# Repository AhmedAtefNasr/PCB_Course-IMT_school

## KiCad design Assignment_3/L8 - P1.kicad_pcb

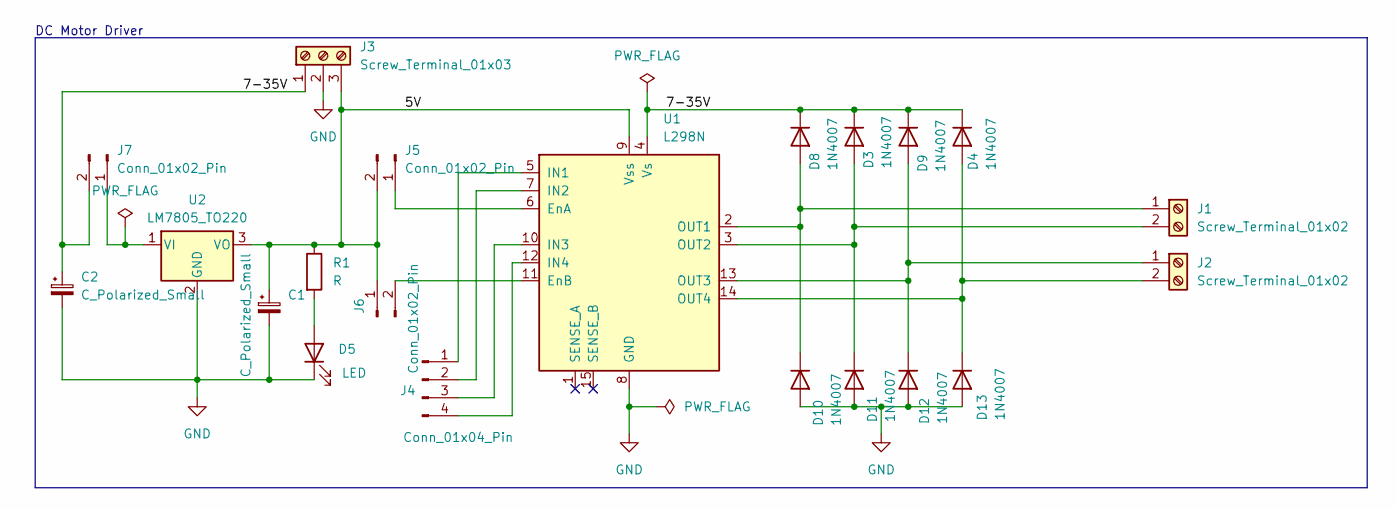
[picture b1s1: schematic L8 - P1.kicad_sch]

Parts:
C1, C2: C_Polarized_Small; CP_Radial_D4.0mm_P1.50mm
D3, D4, D8, D9, D10, D11, D12, D13: 1N4007; D_DO-41_SOD81_P10.16mm_Horizontal
D5: LED; LED_D3.0mm
J1, J2: Screw_Terminal_01x02; TerminalBlock_Phoenix_MPT-0,5-2-2.54_1x02_P2.54mm_Horizontal
J3: Screw_Terminal_01x03; TerminalBlock_Phoenix_MPT-0,5-3-2.54_1x03_P2.54mm_Horizontal
J4: Conn_01x04_Pin; PinHeader_1x04_P1.00mm_Vertical
J5, J6, J7: Conn_01x02_Pin; PinHeader_1x02_P1.00mm_Vertical
R1: R; R_Axial_DIN0204_L3.6mm_D1.6mm_P5.08mm_Horizontal
U1: L298N; TO-220-15_P2.54x5.08mm_StaggerOdd_Lead4.58mm_Vertical
U2: LM7805_TO220; TO-220-3_Horizontal_TabDown

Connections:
/5V: C1.1, J3.3, J5.2, J6.1, R1.1, U1.9 (Vss), U2.3 (VO)
/7-35V: C2.1, D3.1 (K), D4.1 (K), D8.1 (K), D9.1 (K), J3.1, J7.2, U1.4 (Vs)
GND: C1.2, C2.2, D5.1 (K), D10.2 (A), D11.2 (A), D12.2 (A), D13.2 (A), J3.2, U1.8 (GND), U2.2 (GND)
unnamed: D5.2 (A), R1.2
unnamed: D8.2 (A), D10.1 (K), J1.1, U1.2 (OUT1)
unnamed: D3.2 (A), D11.1 (K), J1.2, U1.3 (OUT2)
unnamed: D9.2 (A), D12.1 (K), J2.1, U1.13 (OUT3)
unnamed: D4.2 (A), D13.1 (K), J2.2, U1.14 (OUT4)
unnamed: J4.1, U1.5 (IN1)
unnamed: J4.2, U1.7 (IN2)
unnamed: J4.3, U1.10 (IN3)
unnamed: J4.4, U1.12 (IN4)
unnamed: J5.1, U1.6 (EnA)
unnamed: J6.2, U1.11 (EnB)
unnamed: J7.1, U2.1 (VI)

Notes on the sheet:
DC Motor Driver

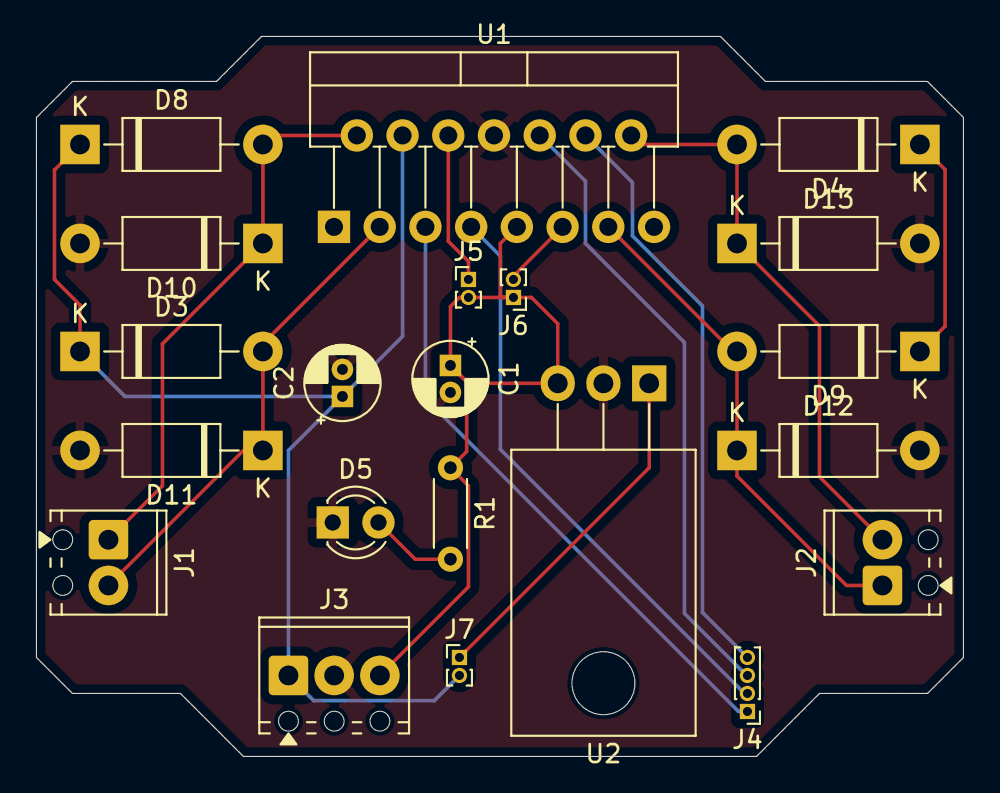
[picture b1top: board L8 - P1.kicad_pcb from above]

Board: 2 copper layers, 51.5 x 40.0 mm, 21 parts (0 on the bottom side), 15 nets.

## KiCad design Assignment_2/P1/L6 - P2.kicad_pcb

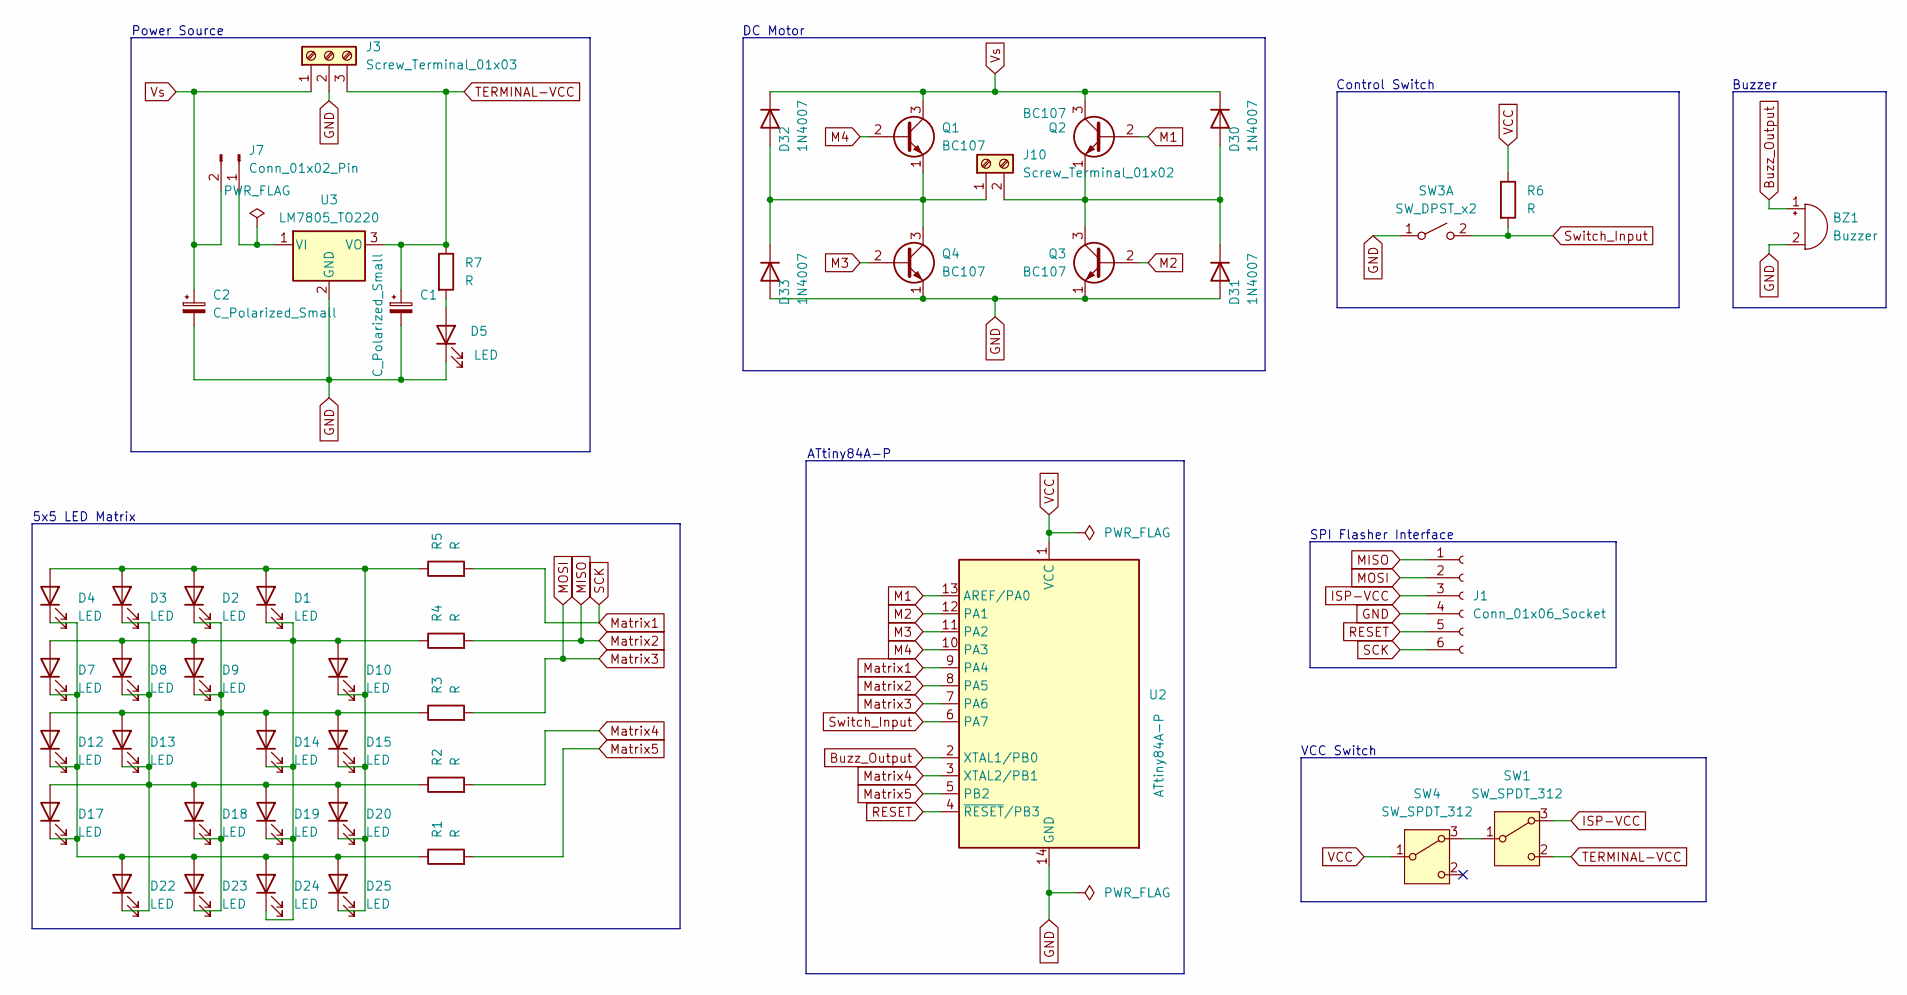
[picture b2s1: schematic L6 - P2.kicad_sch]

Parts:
BZ1: Buzzer; MagneticBuzzer_ProSignal_ABT-410-RC
C1, C2: C_Polarized_Small; CP_Radial_D4.0mm_P1.50mm
D1, D2, D3, D4, D7, D8, D9, D10, D12, D13, D14, D15, D17, D18, D19, D20, D22, D23, D24, D25: LED; LED_D5.0mm_Clear
D5: LED; LED_D3.0mm
D30, D31, D32, D33: 1N4007; D_DO-41_SOD81_P10.16mm_Horizontal
J1: Conn_01x06_Socket; PinHeader_1x06_P2.54mm_Horizontal
J3: Screw_Terminal_01x03; TerminalBlock_Phoenix_MPT-0,5-3-2.54_1x03_P2.54mm_Horizontal
J7: Conn_01x02_Pin; PinHeader_1x02_P1.00mm_Vertical
J10: Screw_Terminal_01x02; TerminalBlock_Phoenix_MPT-0,5-2-2.54_1x02_P2.54mm_Horizontal
Q1, Q2, Q3, Q4: BC107; TO-18-3
R1, R2, R3, R4, R5, R6, R7: R; R_Axial_DIN0204_L3.6mm_D1.6mm_P5.08mm_Horizontal
SW1, SW4: SW_SPDT_312; SW_Slide_SPDT_Straight_CK_OS102011MS2Q
SW3: SW_DPST_x2; SW_PUSH_6mm_H5mm
U2: ATtiny84A-P; DIP-14_W7.62mm
U3: LM7805_TO220; TO-220-3_Horizontal_TabDown

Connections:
Buzz_Output: BZ1.1 (+), U2.2 (XTAL1/PB0)
GND: BZ1.2 (-), C1.2, C2.2, D5.1 (K), D31.2 (A), D33.2 (A), J1.4, J3.2, Q3.1 (E), Q4.1 (E), SW3.1 (A), U2.14 (GND), U3.2 (GND)
ISP-VCC: J1.3, SW1.3 (A)
M1: Q2.2 (B), U2.13 (AREF/PA0)
M2: Q3.2 (B), U2.12 (PA1)
M3: Q4.2 (B), U2.11 (PA2)
M4: Q1.2 (B), U2.10 (PA3)
MISO: J1.1, R4.2, U2.8 (PA5)
MOSI: J1.2, R3.2, U2.7 (PA6)
Matrix1: J1.6, R5.2, U2.9 (PA4)
Matrix4: R2.2, U2.3 (XTAL2/PB1)
Matrix5: R1.2, U2.5 (PB2)
unnamed: D1.2 (A), D2.2 (A), D3.2 (A), D4.2 (A), D10.1 (K), D15.1 (K), D20.1 (K), D25.1 (K), R5.1
unnamed: D1.1 (K), D7.2 (A), D8.2 (A), D9.2 (A), D10.2 (A), D14.1 (K), D19.1 (K), D24.1 (K), R4.1
unnamed: D5.2 (A), R7.2
unnamed: D2.1 (K), D9.1 (K), D12.2 (A), D13.2 (A), D14.2 (A), D15.2 (A), D18.1 (K), D23.1 (K), R3.1
unnamed: D4.1 (K), D7.1 (K), D12.1 (K), D17.1 (K), D22.2 (A), D23.2 (A), D24.2 (A), D25.2 (A), R1.1
unnamed: D3.1 (K), D8.1 (K), D13.1 (K), D17.2 (A), D18.2 (A), D19.2 (A), D20.2 (A), D22.1 (K), R2.1
unnamed: D30.2 (A), D31.1 (K), J10.2, Q2.1 (E), Q3.3 (C)
unnamed: D32.2 (A), D33.1 (K), J10.1, Q1.1 (E), Q4.3 (C)
unnamed: J7.1, U3.1 (VI)
unnamed: SW1.1 (B), SW4.3 (A)
RESET: J1.5, U2.4 (~RESET/PB3)
Switch_Input: R6.2, SW3.2 (B), U2.6 (PA7)
TERMINAL-VCC: C1.1, J3.3, R7.1, SW1.2 (C), U3.3 (VO)
VCC: R6.1, SW4.1 (B), U2.1 (VCC)
Vs: C2.1, D30.1 (K), D32.1 (K), J3.1, J7.2, Q1.3 (C), Q2.3 (C)

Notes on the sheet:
Power Source
Control Switch
Buzzer
5x5 LED Matrix
DC Motor
SPI Flasher Interface
VCC Switch
ATtiny84A-P

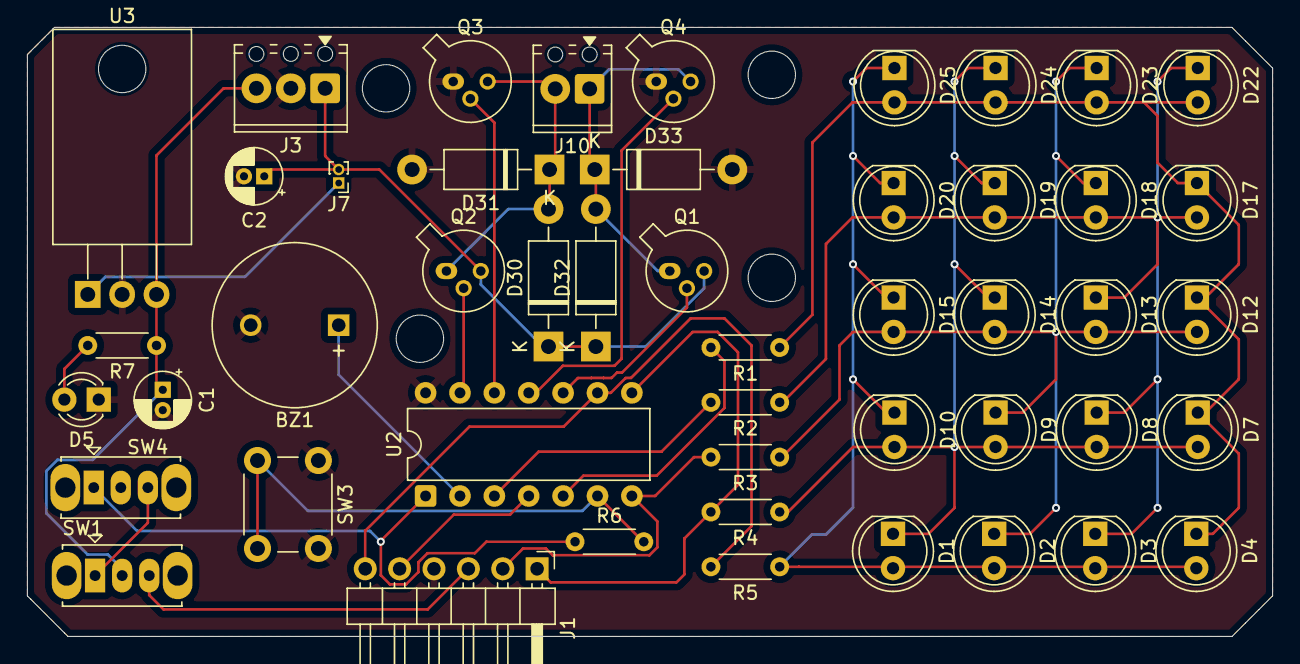
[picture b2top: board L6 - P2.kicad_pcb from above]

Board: 2 copper layers, 92.0 x 45.0 mm, 48 parts (0 on the bottom side), 27 nets.

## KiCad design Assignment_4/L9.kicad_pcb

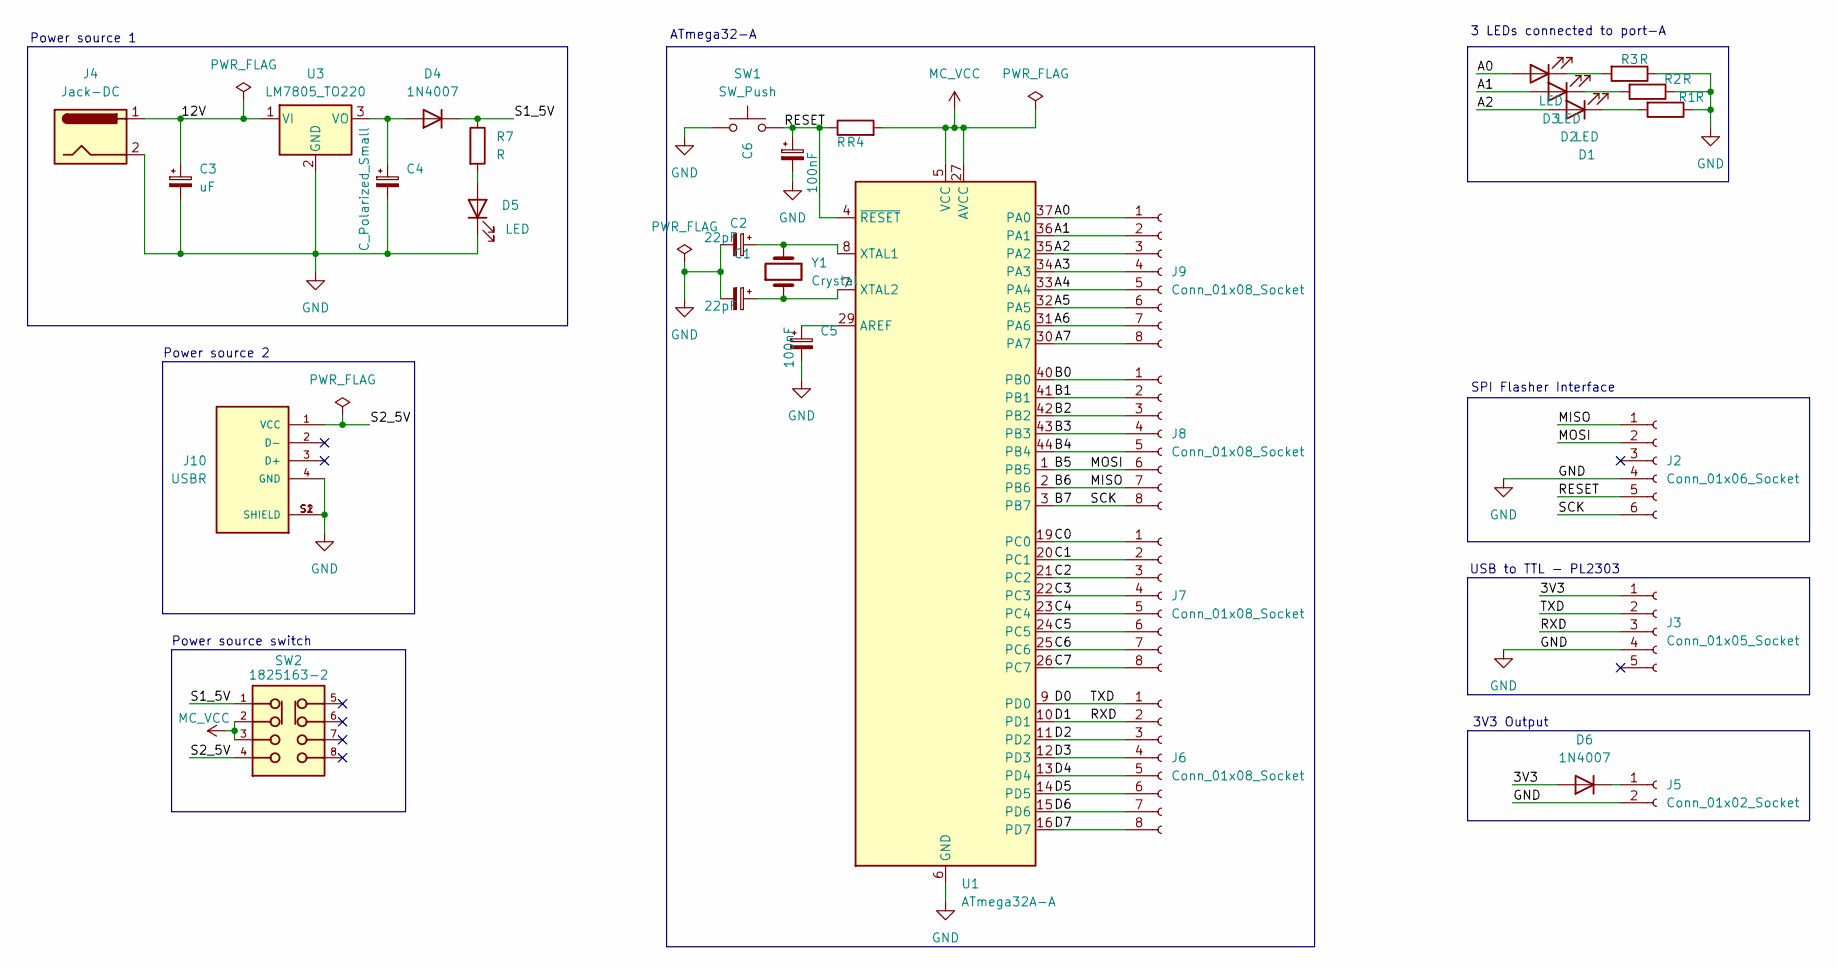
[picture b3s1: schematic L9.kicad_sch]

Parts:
C1, C2: 22pF; C_Disc_D5.1mm_W3.2mm_P5.00mm
C3: uF; CP_Radial_D4.0mm_P1.50mm
C4: C_Polarized_Small; CP_Radial_D4.0mm_P1.50mm
C5, C6: 100nF; C_Disc_D3.0mm_W2.0mm_P2.50mm
D1, D2, D3: LED; LED_D5.0mm
D4, D6: 1N4007; D_DO-41_SOD81_P10.16mm_Horizontal
D5: LED; LED_D3.0mm
J2: Conn_01x06_Socket; PinHeader_1x06_P2.54mm_Horizontal
J3: Conn_01x05_Socket; PinHeader_1x05_P2.54mm_Horizontal
J4: Jack-DC; BarrelJack_Horizontal
J5: Conn_01x02_Socket; PinHeader_1x02_P2.54mm_Vertical
J6, J7, J8, J9: Conn_01x08_Socket; PinSocket_1x08_P2.54mm_Vertical
J10: USBR; SAMTEC_USBR-B-S-S-O-TH; PARTREV M
R1, R2, R3, R4, R7: R; R_Axial_DIN0204_L3.6mm_D1.6mm_P5.08mm_Horizontal
SW1: SW_Push; SW_PUSH_6mm_H5mm
SW2: 1825163-2; SW_1825163-2; PARTREV A3
U1: ATmega32A-A; TQFP-44_10x10mm_P0.8mm
U3: LM7805_TO220; TO-220-3_Horizontal_TabDown
Y1: Crystal; Crystal_HC49-4H_Vertical

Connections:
/3V3: D6.2 (A), J3.1
/12V: C3.1, J4.1, U3.1 (VI)
/A0: D3.2 (A), J9.1, U1.37 (PA0)
/A1: D2.2 (A), J9.2, U1.36 (PA1)
/A2: D1.2 (A), J9.3, U1.35 (PA2)
/A3: J9.4, U1.34 (PA3)
/A4: J9.5, U1.33 (PA4)
/A5: J9.6, U1.32 (PA5)
/A6: J9.7, U1.31 (PA6)
/A7: J9.8, U1.30 (PA7)
/B0: J8.1, U1.40 (PB0)
/B1: J8.2, U1.41 (PB1)
/B2: J8.3, U1.42 (PB2)
/B3: J8.4, U1.43 (PB3)
/B4: J8.5, U1.44 (PB4)
/B5: J2.2, J8.6, U1.1 (PB5)
/B6: J2.1, J8.7, U1.2 (PB6)
/B7: J2.6, J8.8, U1.3 (PB7)
/C0: J7.1, U1.19 (PC0)
/C1: J7.2, U1.20 (PC1)
/C2: J7.3, U1.21 (PC2)
/C3: J7.4, U1.22 (PC3)
/C4: J7.5, U1.23 (PC4)
/C5: J7.6, U1.24 (PC5)
/C6: J7.7, U1.25 (PC6)
/C7: J7.8, U1.26 (PC7)
/D0: J3.2, J6.1, U1.9 (PD0)
/D1: J3.3, J6.2, U1.10 (PD1)
/D2: J6.3, U1.11 (PD2)
/D3: J6.4, U1.12 (PD3)
/D4: J6.5, U1.13 (PD4)
/D5: J6.6, U1.14 (PD5)
/D6: J6.7, U1.15 (PD6)
/D7: J6.8, U1.16 (PD7)
/RESET: C6.1, J2.5, R4.1, SW1.2, U1.4 (~RESET)
/S1_5V: D4.1 (K), R7.1, SW2.1
/S2_5V: J10.1 (VCC), SW2.4
GND: C1.2, C2.2, C3.2, C4.2, C5.2, C6.2, D5.1 (K), J2.4, J3.4, J4.2, J5.2, J10.4 (GND), J10.S1 (SHIELD), J10.S2 (SHIELD), R1.1, R2.1, R3.1, SW1.1, U1.6 (GND), U1.18 (GND), U1.28 (GND), U1.39 (GND), U3.2 (GND)
MC_VCC: R4.2, SW2.2, SW2.3, U1.5 (VCC), U1.17 (VCC), U1.27 (AVCC), U1.38 (VCC)
unnamed: D1.1 (K), R1.2
unnamed: D2.1 (K), R2.2
unnamed: D3.1 (K), R3.2
unnamed: C4.1, D4.2 (A), U3.3 (VO)
unnamed: D5.2 (A), R7.2
unnamed: D6.1 (K), J5.1
unnamed: C5.1, U1.29 (AREF)
unnamed: C2.1, U1.8 (XTAL1), Y1.2
unnamed: C1.1, U1.7 (XTAL2), Y1.1

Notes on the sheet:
ATmega32-A
Power source switch
3V3 Output
Power source 1
USB to TTL - PL2303
SPI Flasher Interface
Power source 2
3 LEDs connected to port-A

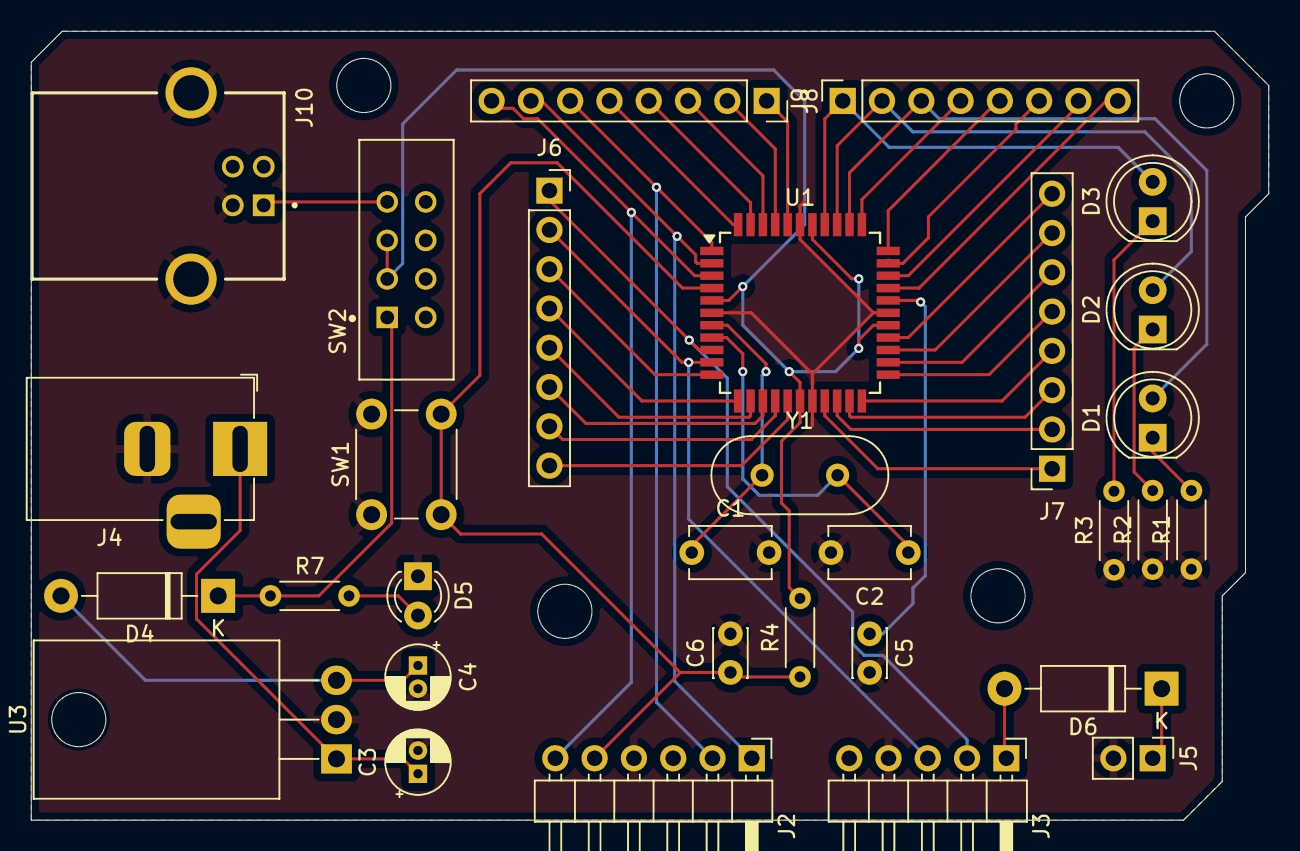
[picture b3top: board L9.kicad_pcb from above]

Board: 2 copper layers, 80.0 x 51.0 mm, 32 parts (1 on the bottom side), 48 nets.

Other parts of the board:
G: LOGO; logo

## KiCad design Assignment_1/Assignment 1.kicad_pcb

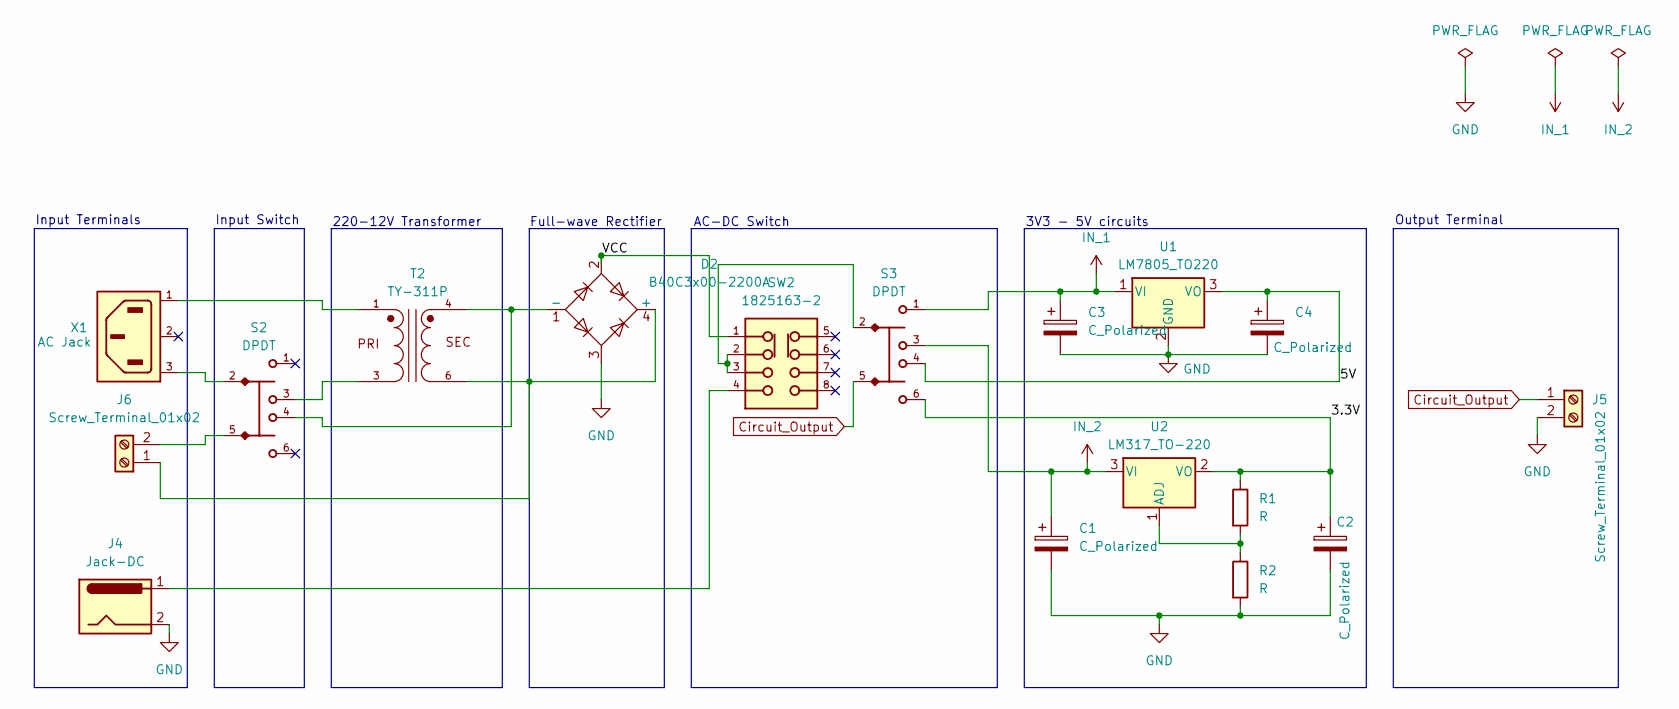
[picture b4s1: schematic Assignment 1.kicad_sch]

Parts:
C1, C2, C3, C4: C_Polarized; CP_Radial_D6.3mm_P2.50mm
D2: B40C3x00-2200A; Diode_Bridge_32.0x5.6x17.0mm_P10.0mm_P7.5mm
J4: Jack-DC; BarrelJack_Horizontal
J5, J6: Screw_Terminal_01x02; TerminalBlock_Phoenix_MKDS-3-2-5.08_1x02_P5.08mm_Horizontal
R1, R2: R; R_Axial_DIN0207_L6.3mm_D2.5mm_P7.62mm_Horizontal
S2, S3: DPDT; 472133010111
SW2: 1825163-2; SW_1825163-2; PARTREV A3
T2: TY-311P; XFMR_TY-311P; PARTREV 2016
U1: LM7805_TO220; TO-220-3_Horizontal_TabDown
U2: LM317_TO-220; TO-220-3_Horizontal_TabDown
X1: AC Jack; 6ESRM-P; MPN 6ESRM-P

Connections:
/3.3V: C2.1, R1.1, S3.6, U2.2 (VO)
/5V: C4.1, S3.4, U1.3 (VO)
/VCC: D2.2, SW2.1
Circuit_Output: J5.1, S3.5
GND: C1.2, C2.2, C3.2, C4.2, D2.3, J4.2, J5.2, R2.2, U1.2 (GND)
IN_1: C3.1, S3.1, U1.1 (VI)
IN_2: C1.1, S3.3, U2.3 (VI)
unnamed: D2.4 (+), J6.1, T2.6
unnamed: D2.1 (-), S2.4, T2.4
unnamed: J4.1, SW2.4
unnamed: J6.2, S2.5
unnamed: S2.2, X1.3
unnamed: S2.3, T2.3
unnamed: S3.2, SW2.2, SW2.3
unnamed: T2.1, X1.1
unnamed: R1.2, R2.1, U2.1 (ADJ)

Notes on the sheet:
Full-wave Rectifier
3V3 - 5V circuits
Input Switch
Output Terminal
220-12V Transformer
AC-DC Switch
Input Terminals

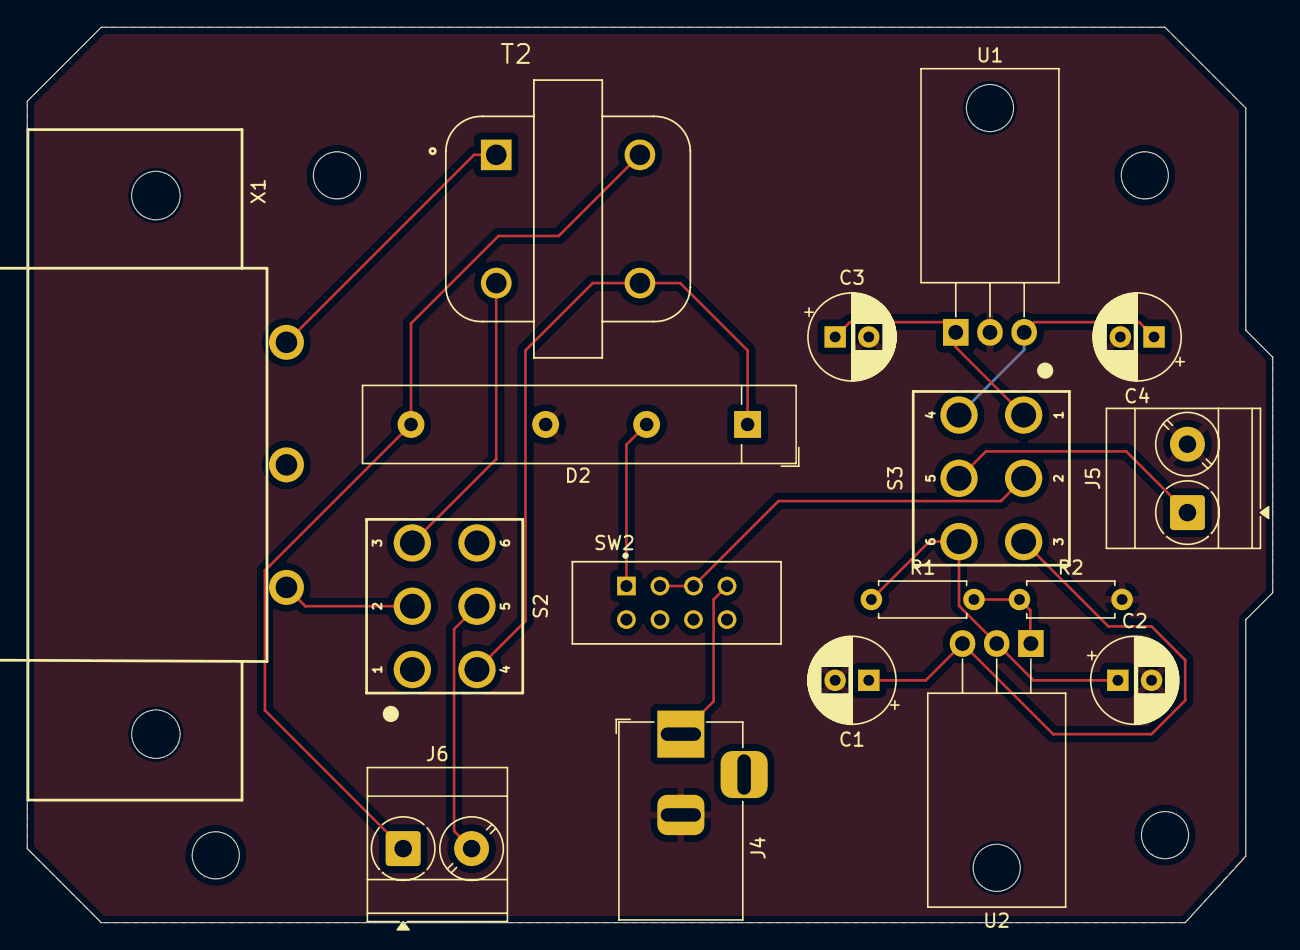
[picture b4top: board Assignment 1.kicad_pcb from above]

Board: 2 copper layers, 92.5 x 66.5 mm, 17 parts (0 on the bottom side), 16 nets.

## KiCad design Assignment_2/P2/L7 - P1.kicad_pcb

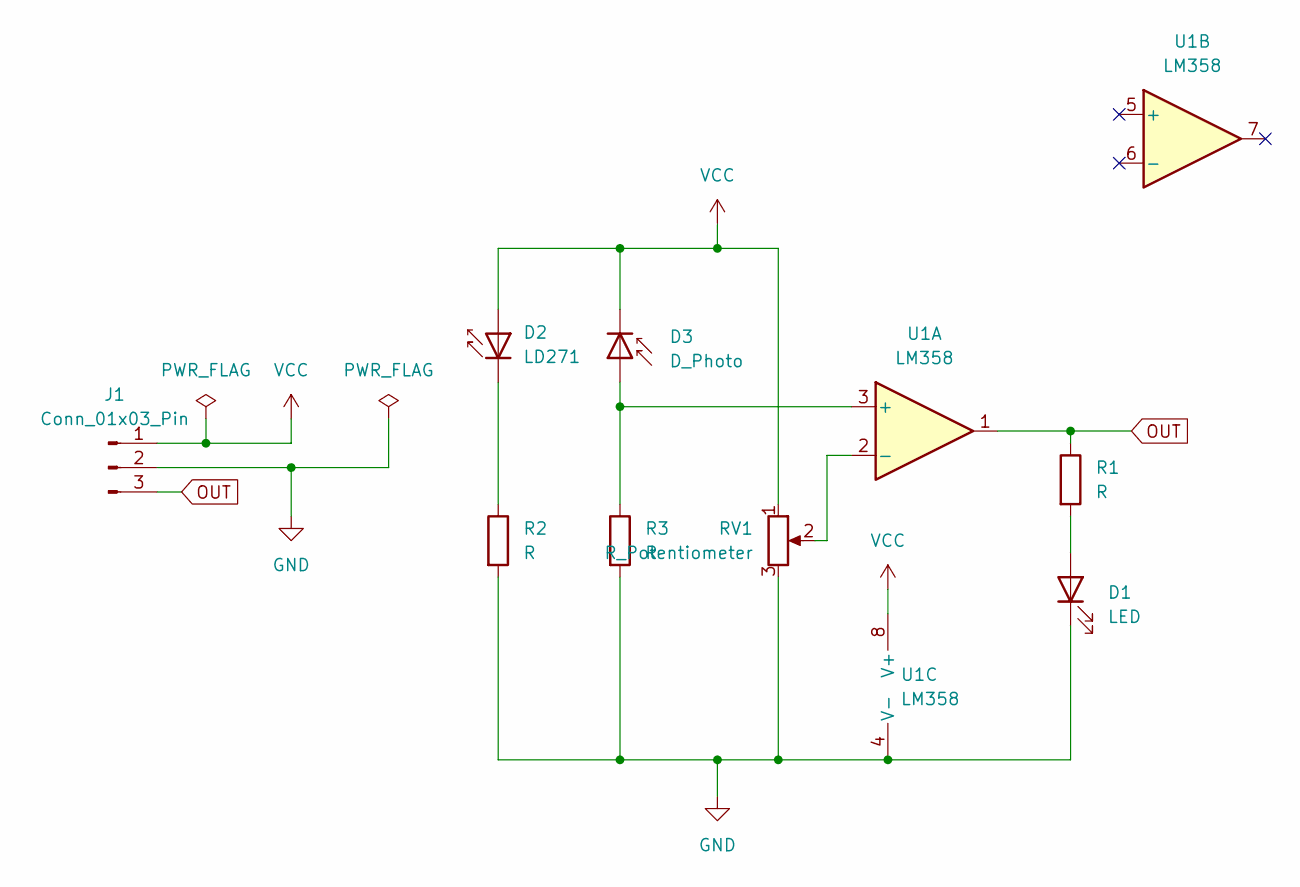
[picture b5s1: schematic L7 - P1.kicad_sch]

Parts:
D1: LED; LED_D5.0mm_Clear
D2: LD271; LED_D5.0mm_Horizontal_O1.27mm_Z3.0mm_IRGrey
D3: D_Photo; LED_D5.0mm_Horizontal_O1.27mm_Z3.0mm_IRBlack
J1: Conn_01x03_Pin; PinHeader_1x03_P1.27mm_Horizontal
R1, R2, R3: R; R_Axial_DIN0207_L6.3mm_D2.5mm_P10.16mm_Horizontal
RV1: R_Potentiometer; Potentiometer_Bourns_3266W_Vertical
U1: LM358; DIP-8_W7.62mm

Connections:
GND: D1.1 (K), J1.2, R2.2, R3.2, RV1.3, U1.4 (V-)
unnamed: D1.2 (A), R1.2
unnamed: D2.1 (K), R2.1
unnamed: D3.2 (A), R3.1, U1.3 (+)
unnamed: RV1.2, U1.2 (-)
OUT: J1.3, R1.1, U1.1
VCC: D2.2 (A), D3.1 (K), J1.1, RV1.1, U1.8 (V+)

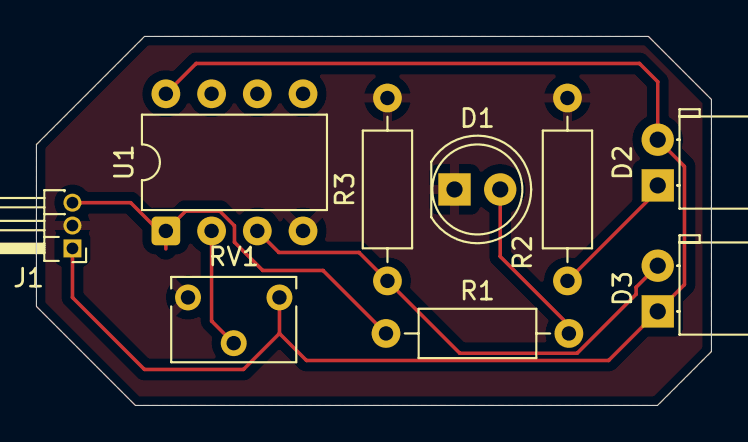
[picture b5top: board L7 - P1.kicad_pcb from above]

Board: 2 copper layers, 37.5 x 20.5 mm, 9 parts (0 on the bottom side), 7 nets.

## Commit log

2025-05-30 Assignment 1 create
2025-05-30 Create Assignment 1 folder
2025-05-30 Update folder name
2025-05-30 Add Assignment 2 - P1
2025-05-30 Add Assignment 2 - P2
2025-05-30 Add Assignment 3
2025-05-30 Add Assignment 4
2025-05-31 Add custom components
2025-05-31 Add custom components for all assignments
2025-05-31 Assignment_4: Add layout P1
2025-05-31 Update layout of all assignments
2025-05-31 Update layout of all assignments - P2
